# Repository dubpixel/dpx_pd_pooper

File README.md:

<!-- Improved compatibility of back to top link: See: https://github.com/othneildrew/Best-README-Template/pull/73 -->

<!--
*** Thanks for checking out the Best-README-Template. If you have a suggestion
*** that would make this better, please fork the repo and create a pull request
*** or simply open an issue with the tag "enhancement".
*** Don't forget to give the project a star!
*** Thanks again! Now go create something AMAZING! :D
*** /// d   u   b   p   i   x   e   l 
*** this has additionally been changed by dubpixel for the dpx_ series of projects
*** search dpx_pd_pooper .. replace COMMAND OPTION F
*** also has added kicad badge
-->

<!-- PROJECT SHIELDS -->
<!--
*** I'm using markdown "reference style" links for readability.
*** Reference links are enclosed in brackets [ ] instead of parentheses ( ).
*** See the bottom of this document for the declaration of the reference variables
*** for contributors-url, forks-url, etc. This is an optional, concise syntax you may use.
*** https://www.markdownguide.org/basic-syntax/#reference-style-links
***
-->
[![Contributors][contributors-shield]][contributors-url]
[![Forks][forks-shield]][forks-url]
[![Stargazers][stars-shield]][stars-url]
[![Issues][issues-shield]][issues-url]
[![MIT License][license-shield]][license-url]
[![LinkedIn][linkedin-shield]][linkedin-url]

<!-- PROJECT LOGO -->
<br />
<div align="center">

<h1 align="center">dpx_pd_pooper </h1>
<h3 align="center"><i>pd poops on tap</i></h3>

  <p align="center">
    ...a basic ch224k pd trigger board w/ usb-c connector
    <br />
    <br />
    <br />
    <br />
    <p align="center">
     <a href="https://github.com/dubpixel/dpx_pd_pooper/tree/main/"><strong>Project Here!</strong></a>
     »  
    <a href="https://github.com/dubpixel/dpx_pd_pooper/tree/main/src/bom"><strong>BOM Here!</strong></a>
     » 
    <a href="https://dubpixel.github.io/dpx_pd_pooper/ebom/index.html"><strong>Interactive BOM Here!</strong></a>
    ·
       <br />
    <a href="https://github.com/dubpixel/dpx_pd_pooper/issues/new?labels=bug&template=bug-report---.md">Report Bug</a>
    ·
    <a href="https://github.com/dubpixel/dpx_pd_pooper/issues/new?labels=enhancement&template=feature-request---.md">Request Feature</a>
    </div>
    </p>
</div>
   <br />
    <br />
    <br />
    <br />
<!-- TABLE OF CONTENTS -->
<details>
  <summary>Table of Contents</summary>
  <ol>
    <li>
      <a href="#about-the-project">About The Project</a>
      <ul>
        <li><a href="#built-with">Built With</a></li>
      </ul>
    </li>
    <li>
      <a href="#getting-started">Getting Started</a>
      <ul>
        <li><a href="#prerequisites">Prerequisites</a></li>
        <li><a href="#installation">Installation</a></li>
      </ul>
    </li>
    <li><a href="#usage">Usage</a></li>
    <li><a href="#roadmap">Roadmap</a></li>
    <li><a href="#contributing">Contributing</a></li>
    <li><a href="#license">License</a></li>
    <li><a href="#contact">Contact</a></li>
    <li><a href="#acknowledgments">Acknowledgments</a></li>
  </ol>
</details>
    <br />
<!-- ABOUT THE PROJECT -->
<details>
  <summary><h3>About The Project</h3></summary>
  proving a basic ch224 pd power trigger IC to be used in forthcoming dubpixel / TNG ENT INC devices

</br>
www.dubpixel.tv  - i@dubpixel.tv
</br>
</details>

FRONT
![FRONT][product-front]

REAR
![REAR][product-rear]

iBOM PCB Front
![iBOM Front][product-pcbFront]

iBOM PCB Rear
![iBOM Front][product-pcbRear]

<p align="right">(<a href="#readme-top">back to top</a>)</p>

### Built With 
* [![KiCad][KiCad.org]][KiCad-url]
<!--
 * [![Next][Next.js]][Next-url]
 * [![React][React.js]][React-url]
 * [![Vue][Vue.js]][Vue-url]
 * [![Angular][Angular.io]][Angular-url]
 * [![Svelte][Svelte.dev]][Svelte-url]
 * [![Laravel][Laravel.com]][Laravel-url]
 * [![Bootstrap][Bootstrap.com]][Bootstrap-url]
 * [![JQuery][JQuery.com]][JQuery-url]
 
-->
<p align="right">(<a href="#readme-top">back to top</a>)</p>

<!-- GETTING STARTED -->
## Getting Started

### Prerequisites

### Installation

1. Download...
2. Enjoy.
3. Repeat as Needed!

<!-- USAGE EXAMPLES -->
## Usage

Use this space to show useful examples of how a project can be used. Additional screenshots, code examples and demos work well in this space. You may also link to more resources.

_For more examples, please refer to the [Documentation](https://example.com)_

<p align="right">(<a href="#readme-top">back to top</a>)</p>

<!-- ROADMAP -->
## Roadmap

- [ ] Feature 1
- [ ] Feature 2
- [ ] Feature 3
    - [ ] Nested Feature

See the [open issues](https://github.com/dubpixel/dpx_pd_pooper/issues) for a full list of proposed features (and known issues).

<p align="right">(<a href="#readme-top">back to top</a>)</p>

<!-- CONTRIBUTING -->
## Contributing

Contributions are what make the open source community such an amazing place to learn, inspire, and create. Any contributions you make are **greatly appreciated**.

If you have a suggestion that would make this better, please fork the repo and create a pull request. You can also simply open an issue with the tag "enhancement".
Don't forget to give the project a star! Thanks again!

1. Fork the Project
2. Create your Feature Branch (`git checkout -b feature/AmazingFeature`)
3. Commit your Changes (`git commit -m 'Add some AmazingFeature'`)
4. Push to the Branch (`git push origin feature/AmazingFeature`)
5. Open a Pull Request

<p align="right">(<a href="#readme-top">back to top</a>)</p>

### Top contributors:

<!-- LICENSE -->
## License

Distributed under the MIT License. See `LICENSE.txt` for more information.

<p align="right">(<a href="#readme-top">back to top</a>)</p>

<!-- CONTACT -->
## Contact

#Joshua Fleitell - i@dubpixel.tv

Project Link: [https://github.com/dubpixel/dpx_pd_pooper](https://github.com/dubpixel/dpx_pd_pooper)

<p align="right">(<a href="#readme-top">back to top</a>)</p>

<!-- ACKNOWLEDGMENTS -->
## Acknowledgments

* 
* 
* 

<p align="right">(<a href="#readme-top">back to top</a>)</p>

<!-- MARKDOWN LINKS & IMAGES -->
<!-- https://www.markdownguide.org/basic-syntax/#reference-style-links -->
[contributors-shield]: https://img.shields.io/github/contributors/dubpixel/dpx_pd_pooper.svg?style=for-the-badge
[contributors-url]: https://github.com/dubpixel/dpx_pd_pooper/graphs/contributors
[forks-shield]: https://img.shields.io/github/forks/gdubpixel/dpx_pd_pooper.svg?style=for-the-badge
[forks-url]: https://github.com/dubpixel/dpx_pd_pooper/network/members
[stars-shield]: https://img.shields.io/github/stars/dubpixel/dpx_pd_pooper.svg?style=for-the-badge
[stars-url]: https://github.com/dubpixel/dpx_pd_pooper/stargazers
[issues-shield]: https://img.shields.io/github/issues/dubpixel/dpx_pd_pooper.svg?style=for-the-badge
[issues-url]: https://github.com/dubpixel/dpx_pd_pooper/issues
[license-shield]: https://img.shields.io/github/license/dubpixel/dpx_pd_pooper.svg?style=for-the-badge
[license-url]: https://github.com/dubpixel/dpx_pd_pooper/blob/master/LICENSE.txt
[linkedin-shield]: https://img.shields.io/badge/-LinkedIn-black.svg?style=for-the-badge&logo=linkedin&colorB=555
[linkedin-url]: https://linkedin.com/in/jfleitell
[product-screenshot]: images/screenshot.png
[product-front]: images/front.png
[product-rear]: images/rear.png
[product-pcbFront]: images/pcb_front.png
[product-pcbRear]: images/pcb_rear.png
[Next.js]: https://img.shields.io/badge/next.js-000000?style=for-the-badge&logo=nextdotjs&logoColor=white
[Next-url]: https://nextjs.org/
[React.js]: https://img.shields.io/badge/React-20232A?style=for-the-badge&logo=react&logoColor=61DAFB
[React-url]: https://reactjs.org/
[Vue.js]: https://img.shields.io/badge/Vue.js-35495E?style=for-the-badge&logo=vuedotjs&logoColor=4FC08D
[Vue-url]: https://vuejs.org/
[Angular.io]: https://img.shields.io/badge/Angular-DD0031?style=for-the-badge&logo=angular&logoColor=white
[Angular-url]: https://angular.io/
[Svelte.dev]: https://img.shields.io/badge/Svelte-4A4A55?style=for-the-badge&logo=svelte&logoColor=FF3E00
[Svelte-url]: https://svelte.dev/
[Laravel.com]: https://img.shields.io/badge/Laravel-FF2D20?style=for-the-badge&logo=laravel&logoColor=white
[Laravel-url]: https://laravel.com
[Bootstrap.com]: https://img.shields.io/badge/Bootstrap-563D7C?style=for-the-badge&logo=bootstrap&logoColor=white
[Bootstrap-url]: https://getbootstrap.com
[JQuery.com]: https://img.shields.io/badge/jQuery-0769AD?style=for-the-badge&logo=jquery&logoColor=white
[JQuery-url]: https://jquery.com 
[KiCad.org]: https://img.shields.io/badge/KiCad-v8.0.6-blue
[KiCad-url]: https://kicad.org

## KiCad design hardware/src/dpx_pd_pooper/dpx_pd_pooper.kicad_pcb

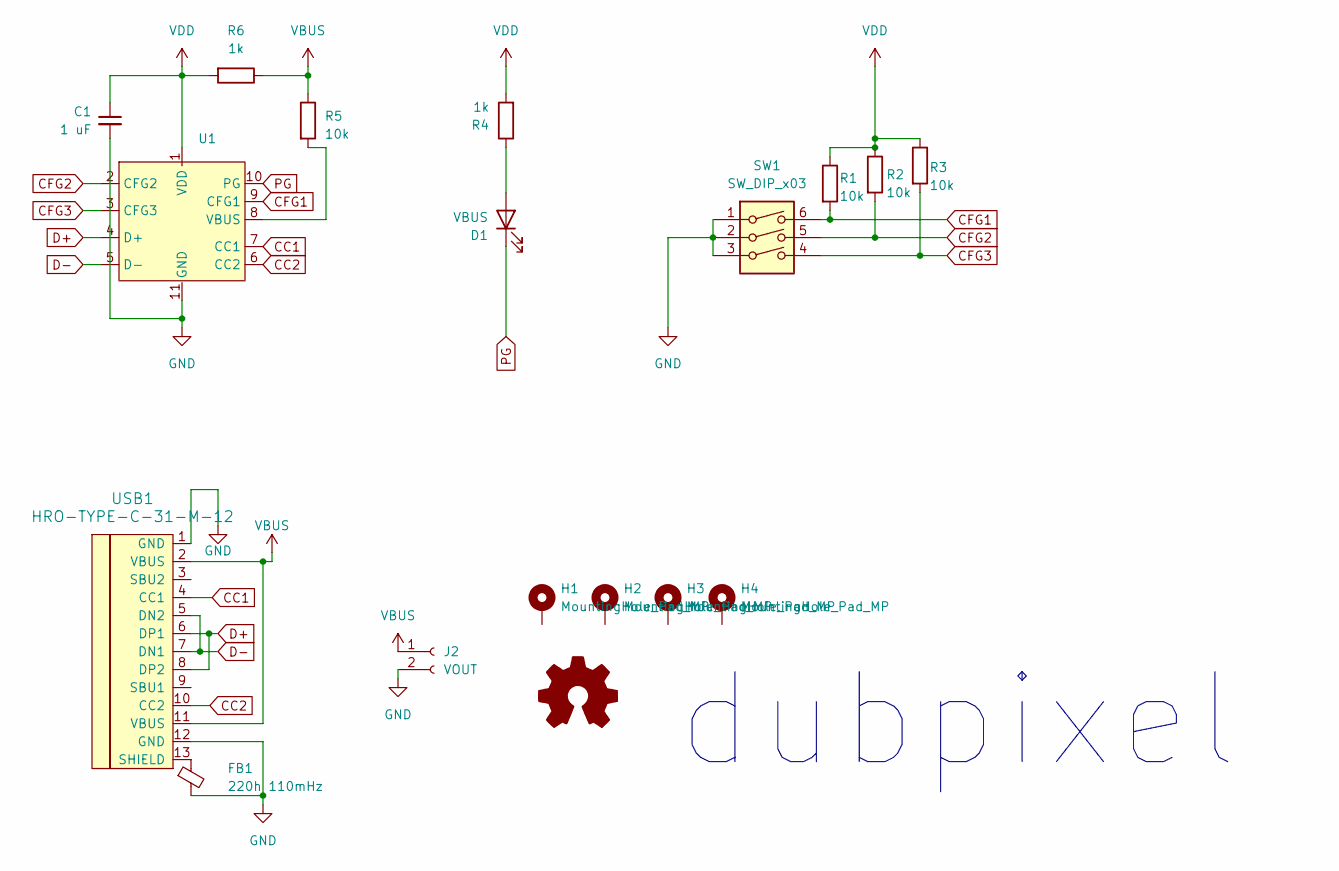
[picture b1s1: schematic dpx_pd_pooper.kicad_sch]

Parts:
C1: 1 uF; C_0603_1608Metric_Pad1.08x0.95mm_HandSolder; LCSC C15849
D1: VBUS; LED_0805_2012Metric_Pad1.15x1.40mm_HandSolder; LCSC C2297
FB1: 220h 110mHz; FERRITE_0603; LCSC C80165
H1, H2, H3, H4: MountingHole_Pad_MP; MountingHole_2.2mm_M2_ISO7380_Pad_TopBottom
J2: VOUT; TerminalBlock_Phoenix_MKDS-1,5-2-5.08_1x02_P5.08mm_Horizont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
R1, R2, R3, R5: 10k; R_0805_2012Metric_Pad1.20x1.40mm_HandSolder; LCSC C17414
R4, R6: 1k; R_0805_2012Metric_Pad1.20x1.40mm_HandSolder; LCSC C17513
SW1: SW_DIP_x03; SP-03P; LCSC C5160895
SYM1: Logo_Open_Hardware_Small; OSHW-LogoNT_7.3x6mm_Silk
U1: SSOP-10-1EP_3.9x4.9mm_P1mm_EP2.1x3.3mm_ThermalVias; LCSC C970725
USB1: HRO-TYPE-C-31-M-12; HRO-TYPE-C-31-M-12-Assembly; LCSC C165948

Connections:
CC1: U1.7 (CC1), USB1.4 (CC1)
CC2: U1.6 (CC2), USB1.10 (CC2)
CFG1: R1.2, SW1.6, U1.9 (CFG1)
CFG2: R2.2, SW1.5, U1.2 (CFG2)
CFG3: R3.2, SW1.4, U1.3 (CFG3)
D+: U1.4 (D+), USB1.6 (DP1), USB1.8 (DP2)
D-: U1.5 (D-), USB1.5 (DN2), USB1.7 (DN1)
GND: C1.2, FB1.2, J2.2, SW1.1, SW1.2, SW1.3, U1.11 (GND), USB1.1 (GND), USB1.12 (GND)
unnamed: D1.2 (A), R4.1
unnamed: R5.2, U1.8 (VBUS)
unnamed: FB1.1, USB1.13 (SHIELD)
PG: D1.1 (K), U1.10 (PG)
VBUS: J2.1, R5.1, R6.1, USB1.2 (VBUS), USB1.11 (VBUS)
VDD: C1.1, R1.1, R2.1, R3.1, R4.2, R6.2, U1.1 (VDD)

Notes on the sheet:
dubpixel

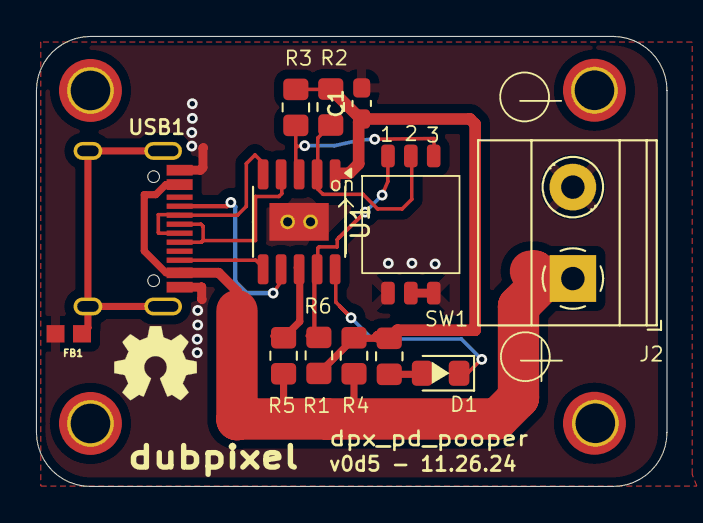
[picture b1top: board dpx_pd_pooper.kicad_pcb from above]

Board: 2 copper layers, 35.0 x 25.0 mm, 18 parts (0 on the bottom side), 14 nets.

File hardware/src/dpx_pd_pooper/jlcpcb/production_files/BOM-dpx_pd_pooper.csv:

Comment,Designator,Footprint,LCSC,Quantity
1 uF,C1,C_0603_1608Metric_Pad1.08x0.95mm_HandSolder,C15849,1
HRO-TYPE-C-31-M-12,USB1,HRO-TYPE-C-31-M-12-Assembly,C165948,1
10k,"R1,R2,R3,R5",R_0805_2012Metric_Pad1.20x1.40mm_HandSolder,C17414,4
1k,"R4,R6",R_0805_2012Metric_Pad1.20x1.40mm_HandSolder,C17513,2
VBUS,D1,LED_0805_2012Metric_Pad1.15x1.40mm_HandSolder,C2297,1
SW_DIP_x03,SW1,SP-03P,C5160895,1
220h 110mHz,FB1,FERRITE_0603,C80165,1
CH224K,U1,SSOP-10-1EP_3.9x4.9mm_P1mm_EP2.1x3.3mm_ThermalVias,C970725,1
VOUT,J2,"TerminalBlock_Phoenix_MKDS-1,5-2-5.08_1x02_P5.08mm_Horizontal",,1

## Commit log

2024-12-08 Update README.md
    whoops~
2024-12-08 Update README.md
    again...
2024-12-09 Update README.md
    more dumb mistakes in the template
2024-12-09 ibom and images
    update ibom and product images
2024-12-15 updated production files
    qr code and some fixes
2024-12-15 lol missing the CH224K ?
